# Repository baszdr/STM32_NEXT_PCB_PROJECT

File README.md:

# STM32_NEXT_PCB_PROJECT
Designed a compact embedded system integrating USB-C, power management, and RF design into a single 4-layer PCB. Focused on clean layout, strong signal integrity, and practical debugging structure. 
💡 Features: 
• STM32WB55 (BLE)
• USB-C with protection
• 3.3V regulation 
• RF matching + U.FL • SWD debugging  
🤝 Sponsored by NextPCB "https://www.nextpcb.com
"

<div align="center">
  
</div>

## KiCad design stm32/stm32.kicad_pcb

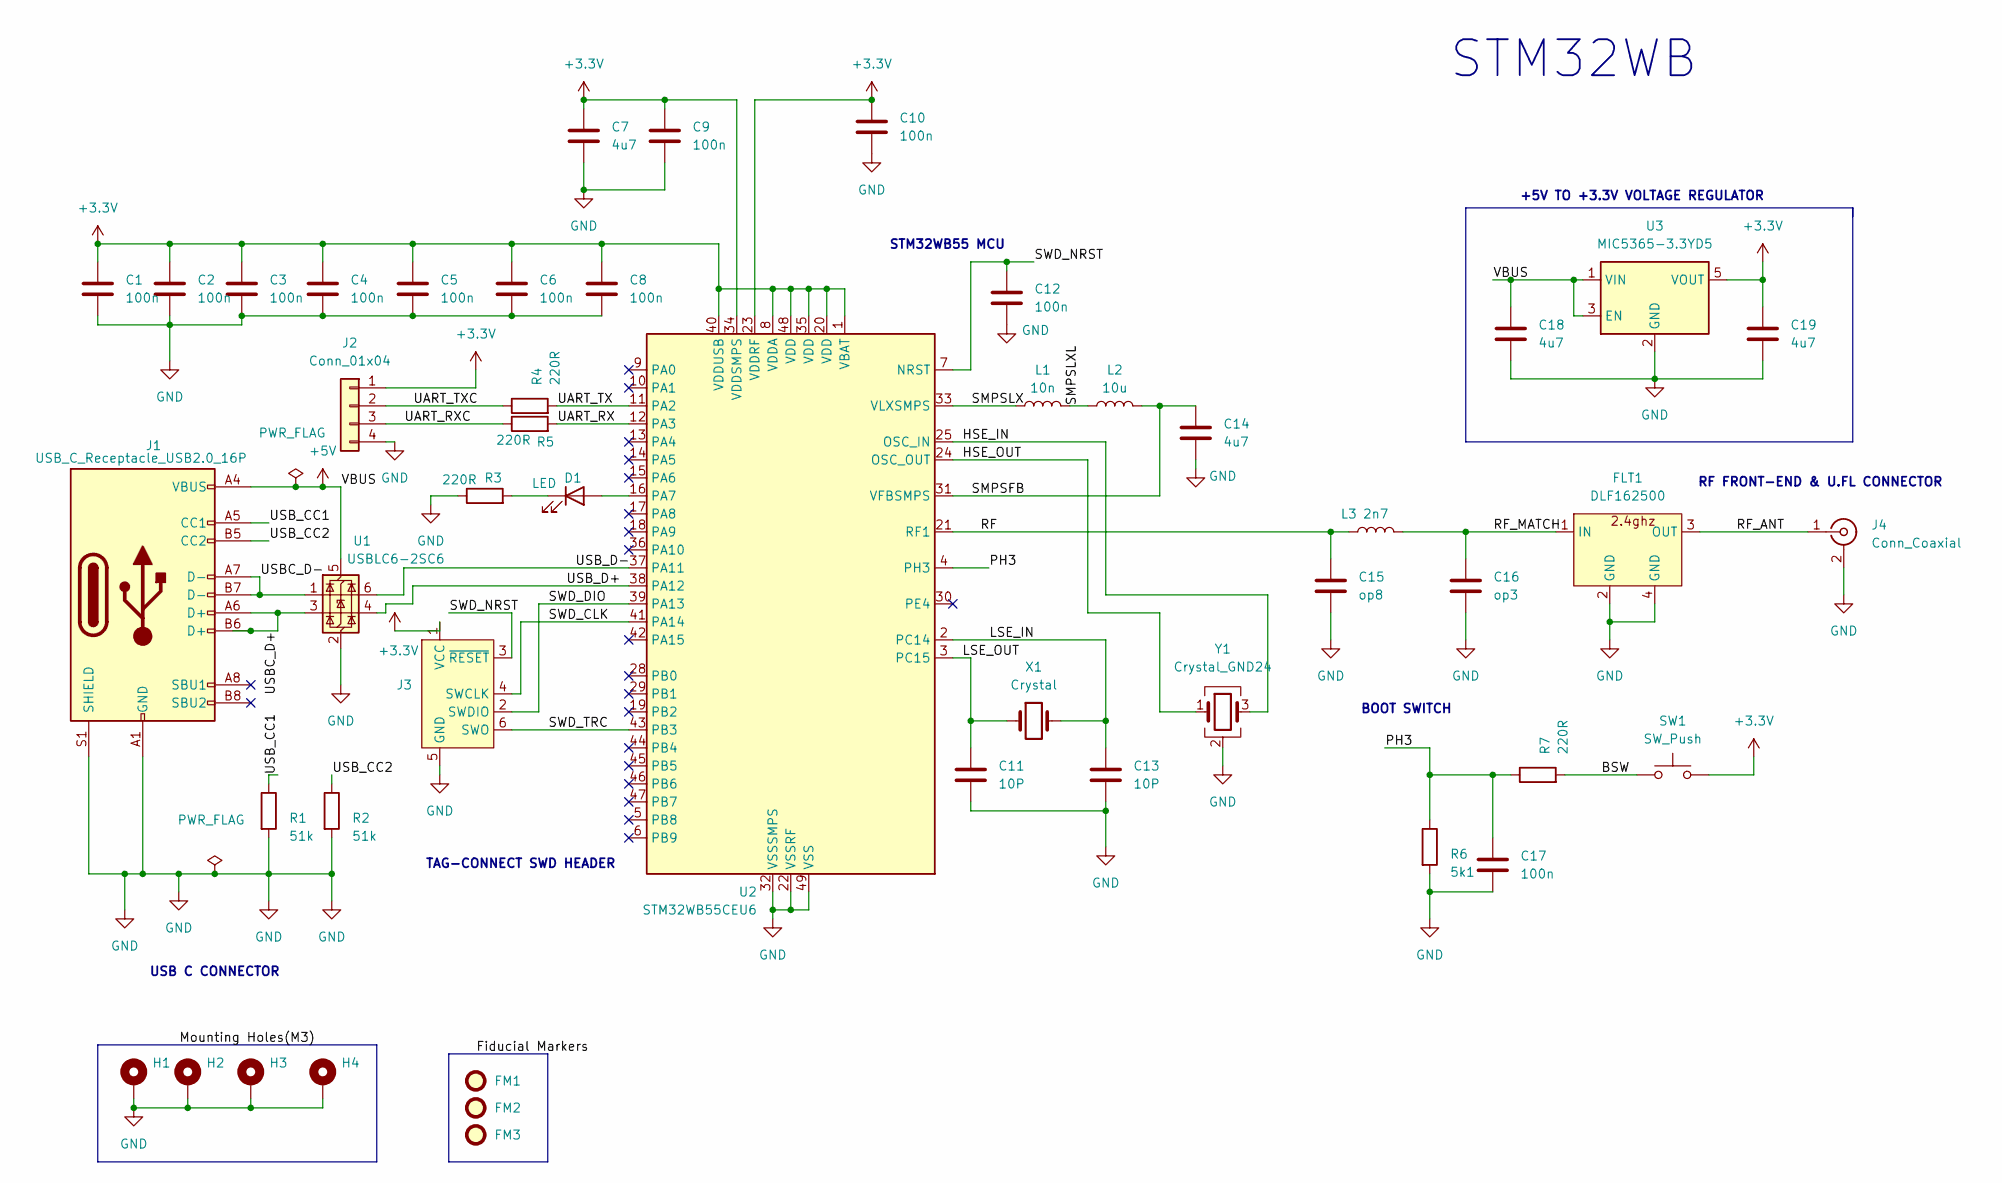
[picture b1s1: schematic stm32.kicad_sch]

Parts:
C1, C2, C3, C4, C5, C6, C8, C9, C10, C12, C17: 100n; C_0402_1005Metric
C7: 4u7; R_0402_1005Metric
C11, C13: 10P; C_0402_1005Metric
C14, C18, C19: 4u7; C_0603_1608Metric
C15: op8; C_0402_1005Metric
C16: op3; C_0402_1005Metric
D1: LED; L_0402_1005Metric
FLT1: DLF162500; Untitled
FM1, FM2, FM3: Fiducial; Fiducial_1mm_Mask2mm
H1, H2, H3, H4: MountingHole_Pad; MountingHole_2.2mm_M2_Pad_Via
J1: USB_C_Receptacle_USB2.0_16P; USB_C_Receptacle_GCT_USB4105-xx-A_16P_TopMnt_Horizontal
J2: Conn_01x04; Molex_CLIK-Mate_502386-0470_1x04-1MP_P1.25mm_Horizontal
J3: Tag-Connect_TC2030-IDC-FP_2x03_P1.27mm_Vertical
J4: Conn_Coaxial; U.FL_Hirose_U.FL-R-SMT-1_Vertical
L1: 10n; L_0402_1005Metric
L2: 10u; L_0402_1005Metric
L3: 2n7; L_0402_1005Metric
R1, R2: 51k; R_0402_1005Metric
R3, R4, R5, R7: 220R; R_0402_1005Metric
R6: 5k1; R_0402_1005Metric
SW1: SW_Push; SW_SPST_CK_RS282G05A3
U1: USBLC6-2SC6; SOT-23-6
U2: STM32WB55CEU6; QFN-48-1EP_7x7mm_P0.5mm_EP5.6x5.6mm
U3: MIC5365-3.3YD5; TSOT-23-5
X1: Crystal; Crystal_SMD_2012-2Pin_2.0x1.2mm
Y1: Crystal_GND24; Crystal_SMD_2016-4Pin_2.0x1.6mm

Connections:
+3.3V: C1.1, C2.1, C3.1, C4.1, C5.1, C6.1, C7.1, C8.1, C9.1, C10.1, C19.1, J2.1, J3.1 (VCC), SW1.2, U2.1 (VBAT), U2.8 (VDDA), U2.20 (VDD), U2.23 (VDDRF), U2.34 (VDDSMPS), U2.35 (VDD), U2.40 (VDDUSB), U2.48 (VDD), U3.5 (VOUT)
+5V: C18.1, J1.A4 (VBUS), J1.A9 (VBUS), J1.B4 (VBUS), J1.B9 (VBUS), U1.5 (VBUS), U3.1 (VIN), U3.3 (EN)
/BSW: R7.2, SW1.1
/HSE_IN: U2.25 (OSC_IN), Y1.3
/HSE_OUT: U2.24 (OSC_OUT), Y1.1
/LSE_IN: C13.1, U2.2 (PC14), X1.2
/LSE_OUT: C11.1, U2.3 (PC15), X1.1
/PH3: C17.1, R6.1, R7.1, U2.4 (PH3)
/RF: C15.1, L3.1, U2.21 (RF1)
/RF_ANT: FLT1.3 (OUT), J4.1 (In)
/RF_MATCH: C16.1, FLT1.1 (IN), L3.2
/SMPSFB: C14.1, L2.2, U2.31 (VFBSMPS)
/SMPSLX: L1.1, U2.33 (VLXSMPS)
/SMPSLXL: L1.2, L2.1
/SWD_CLK: J3.4 (SWCLK), U2.41 (PA14)
/SWD_DIO: J3.2 (SWDIO), U2.39 (PA13)
/SWD_NRST: C12.1, J3.3 (~RESET), U2.7 (NRST)
/SWD_TRC: J3.6 (SWO), U2.43 (PB3)
/UART_RX: R5.2, U2.12 (PA3)
/UART_RXC: J2.3, R5.1
/UART_TX: R4.2, U2.11 (PA2)
/UART_TXC: J2.2, R4.1
/USBC_D+: J1.A6 (D+), J1.B6 (D+), U1.3 (I/O2)
/USBC_D-: J1.A7 (D-), J1.B7 (D-), U1.1 (I/O1)
/USB_CC1: J1.A5 (CC1), R1.1
/USB_CC2: J1.B5 (CC2), R2.1
/USB_D+: U1.4 (I/O2), U2.38 (PA12)
/USB_D-: U1.6 (I/O1), U2.37 (PA11)
GND: C1.2, C2.2, C3.2, C4.2, C5.2, C6.2, C7.2, C8.2, C9.2, C10.2, C11.2, C12.2, C13.2, C14.2, C15.2, C16.2, C17.2, C18.2, C19.2, FLT1.2 (GND), FLT1.4 (GND), H1.1, H2.1, H3.1, H4.1, J1.A1 (GND), J1.A12 (GND), J1.B1 (GND), J1.B12 (GND), J1.S1 (SHIELD), J2.4, J3.5 (GND), J4.2 (Ext), R1.2, R2.2, R3.1, R6.2, U1.2 (GND), U2.22 (VSSRF), U2.32 (VSSSMPS), U2.49 (VSS), U3.2 (GND), Y1.2 (G), Y1.4 (G)
unnamed: D1.2 (A), U2.16 (PA7)
unnamed: D1.1 (K), R3.2

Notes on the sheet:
+5V TO +3.3V VOLTAGE REGULATOR
RF FRONT-END & U.FL CONNECTOR
TAG-CONNECT SWD HEADER
USB C CONNECTOR
STM32WB
STM32WB55 MCU
BOOT SWITCH

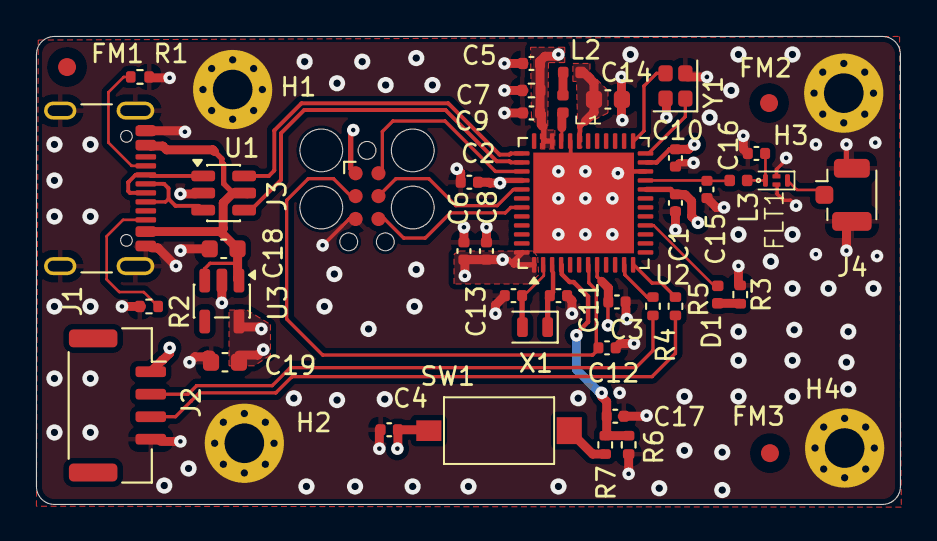
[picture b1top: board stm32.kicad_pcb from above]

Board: 4 copper layers, 48.0 x 26.0 mm, 48 parts (0 on the bottom side), 31 nets.
